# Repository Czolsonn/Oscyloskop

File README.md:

# Oscyloskop
Projekt amatorskiego oscyloskopu z wyświetlaczem LCD

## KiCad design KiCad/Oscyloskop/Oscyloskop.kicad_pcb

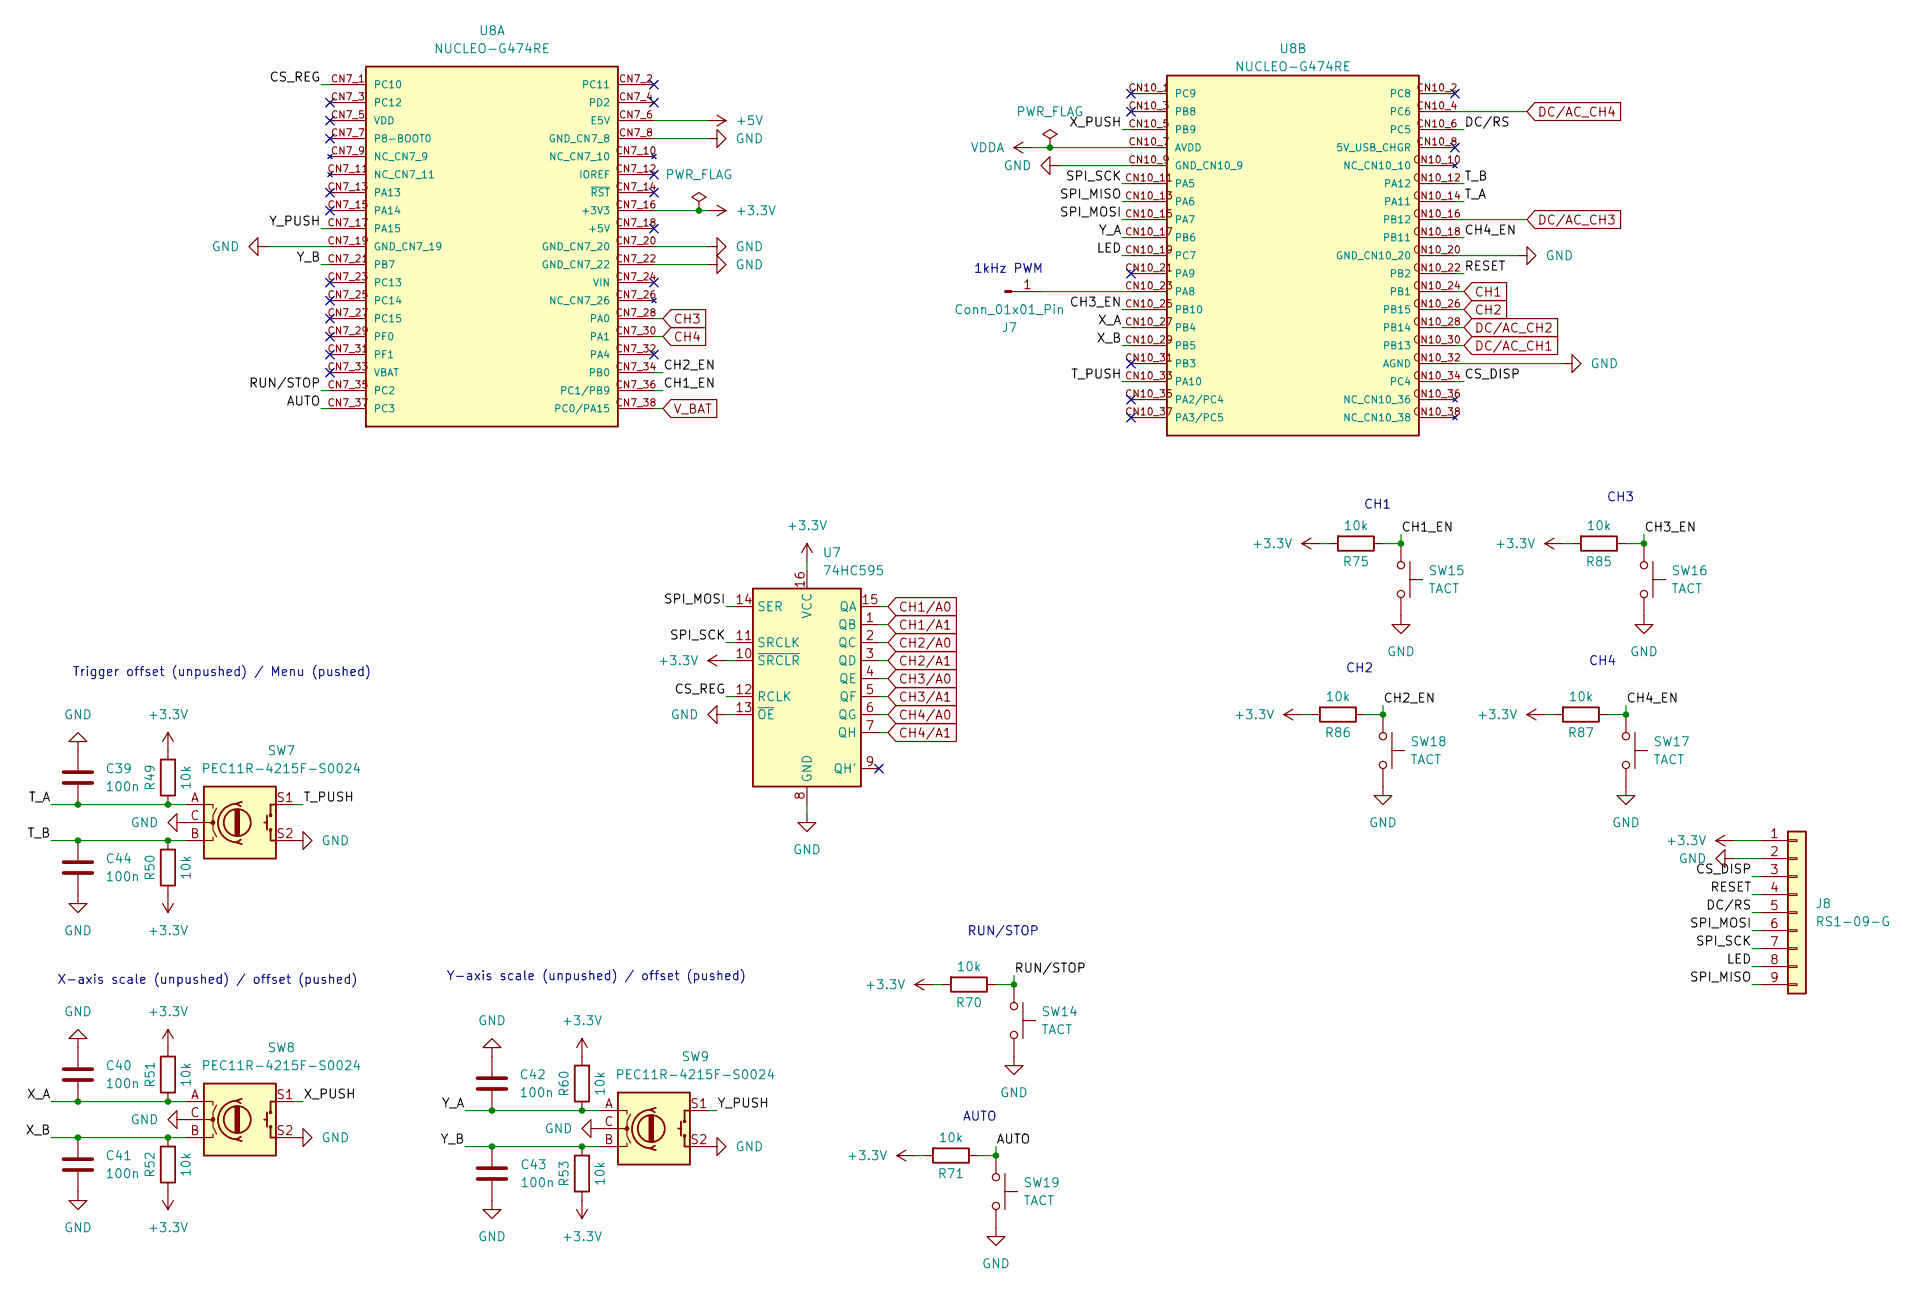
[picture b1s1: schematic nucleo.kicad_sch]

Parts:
C39, C40, C41, C42, C43, C44: 100n; C_0603_1608Metric
J7: Conn_01x01_Pin; PinHeader_1x01_P2.54mm_Vertical
J8: RS1-09-G; PinSocket_1x09_P2.54mm_Vertical
R49, R50, R51, R52, R53, R60, R70, R71, R75, R85, R86, R87: 10k; R_0603_1608Metric
SW7, SW8, SW9: PEC11R-4215F-S0024; RotaryEncoder_EC11_Switch_Vertical_Generic
SW14, SW15, SW16, SW17, SW18, SW19: TACT; SW_PUSH-12mm
U7: 74HC595; TSSOP-16_4.4x5mm_P0.65mm
U8: NUCLEO-G474RE; MODULE_NUCLEO-G474RE; PARTREV 17

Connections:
+3.3V: J8.1, R49.2, R50.1, R51.2, R52.1, R53.1, R60.2, R70.2, R71.2, R75.2, R85.2, R86.2, R87.2, U7.10 (~SRCLR), U7.16 (VCC), U8.CN7_16 (+3V3); also elsewhere on the board
+5V: U8.CN7_6 (E5V); also elsewhere on the board
/Nucleo STM32/AUTO: R71.1, SW19.1, U8.CN7_37 (PC3)
/Nucleo STM32/CH1_EN: R75.1, SW15.1, U8.CN7_36 (PC1/PB9)
/Nucleo STM32/CH2_EN: R86.1, SW18.1, U8.CN7_34 (PB0)
/Nucleo STM32/CH3_EN: R85.1, SW16.1, U8.CN10_25 (PB10)
/Nucleo STM32/CH4_EN: R87.1, SW17.1, U8.CN10_18 (PB11)
/Nucleo STM32/CS_DISP: J8.3, U8.CN10_34 (PC4)
/Nucleo STM32/CS_REG: U7.12 (RCLK), U8.CN7_1 (PC10)
/Nucleo STM32/DC/RS: J8.5, U8.CN10_6 (PC5)
/Nucleo STM32/LED: J8.8, U8.CN10_19 (PC7)
/Nucleo STM32/RESET: J8.4, U8.CN10_22 (PB2)
/Nucleo STM32/RUN/STOP: R70.1, SW14.1, U8.CN7_35 (PC2)
/Nucleo STM32/SPI_MISO: J8.9, U8.CN10_13 (PA6)
/Nucleo STM32/SPI_MOSI: J8.6, U7.14 (SER), U8.CN10_15 (PA7)
/Nucleo STM32/SPI_SCK: J8.7, U7.11 (SRCLK), U8.CN10_11 (PA5)
/Nucleo STM32/T_A: C39.1, R49.1, SW7.A, U8.CN10_14 (PA11)
/Nucleo STM32/T_B: C44.2, R50.2, SW7.B, U8.CN10_12 (PA12)
/Nucleo STM32/T_PUSH: SW7.S1, U8.CN10_33 (PA10)
/Nucleo STM32/X_A: C40.1, R51.1, SW8.A, U8.CN10_27 (PB4)
/Nucleo STM32/X_B: C41.2, R52.2, SW8.B, U8.CN10_29 (PB5)
/Nucleo STM32/X_PUSH: SW8.S1, U8.CN10_5 (PB9)
/Nucleo STM32/Y_A: C42.1, R60.1, SW9.A, U8.CN10_17 (PB6)
/Nucleo STM32/Y_B: C43.2, R53.2, SW9.B, U8.CN7_21 (PB7)
/Nucleo STM32/Y_PUSH: SW9.S1, U8.CN7_17 (PA15)
CH1: U8.CN10_24 (PB1); also elsewhere on the board
CH1/A0: U7.15 (QA); also elsewhere on the board
CH1/A1: U7.1 (QB); also elsewhere on the board
CH2: U8.CN10_26 (PB15); also elsewhere on the board
CH2/A0: U7.2 (QC); also elsewhere on the board
CH2/A1: U7.3 (QD); also elsewhere on the board
CH3: U8.CN7_28 (PA0); also elsewhere on the board
CH3/A0: U7.4 (QE); also elsewhere on the board
CH3/A1: U7.5 (QF); also elsewhere on the board
CH4: U8.CN7_30 (PA1); also elsewhere on the board
CH4/A0: U7.6 (QG); also elsewhere on the board
CH4/A1: U7.7 (QH); also elsewhere on the board
DC/AC_CH1: U8.CN10_30 (PB13); also elsewhere on the board
DC/AC_CH2: U8.CN10_28 (PB14); also elsewhere on the board
DC/AC_CH3: U8.CN10_16 (PB12); also elsewhere on the board
DC/AC_CH4: U8.CN10_4 (PC6); also elsewhere on the board
GND: C39.2, C40.2, C41.1, C42.2, C43.1, C44.1, J8.2, SW7.C, SW7.S2, SW8.C, SW8.S2, SW9.C, SW9.S2, SW14.2, SW15.2, SW16.2, SW17.2, SW18.2, SW19.2, U7.8 (GND), U7.13 (~OE), U8.CN7_8 (GND_CN7_8), U8.CN7_19 (GND_CN7_19), U8.CN7_20 (GND_CN7_20), U8.CN7_22 (GND_CN7_22), U8.CN10_9 (GND_CN10_9), U8.CN10_20 (GND_CN10_20), U8.CN10_32 (AGND); also elsewhere on the board
unnamed: J7.1 (Pin_1_1), U8.CN10_23 (PA8)
VDDA: U8.CN10_7 (AVDD); also elsewhere on the board
V_BAT: U8.CN7_38 (PC0/PA15); also elsewhere on the board

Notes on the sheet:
Y-axis scale (unpushed) / offset (pushed)
CH2
RUN/STOP
CH1
1kHz PWM
AUTO
CH4
X-axis scale (unpushed) / offset (pushed)
Trigger offset (unpushed) / Menu (pushed)
CH3

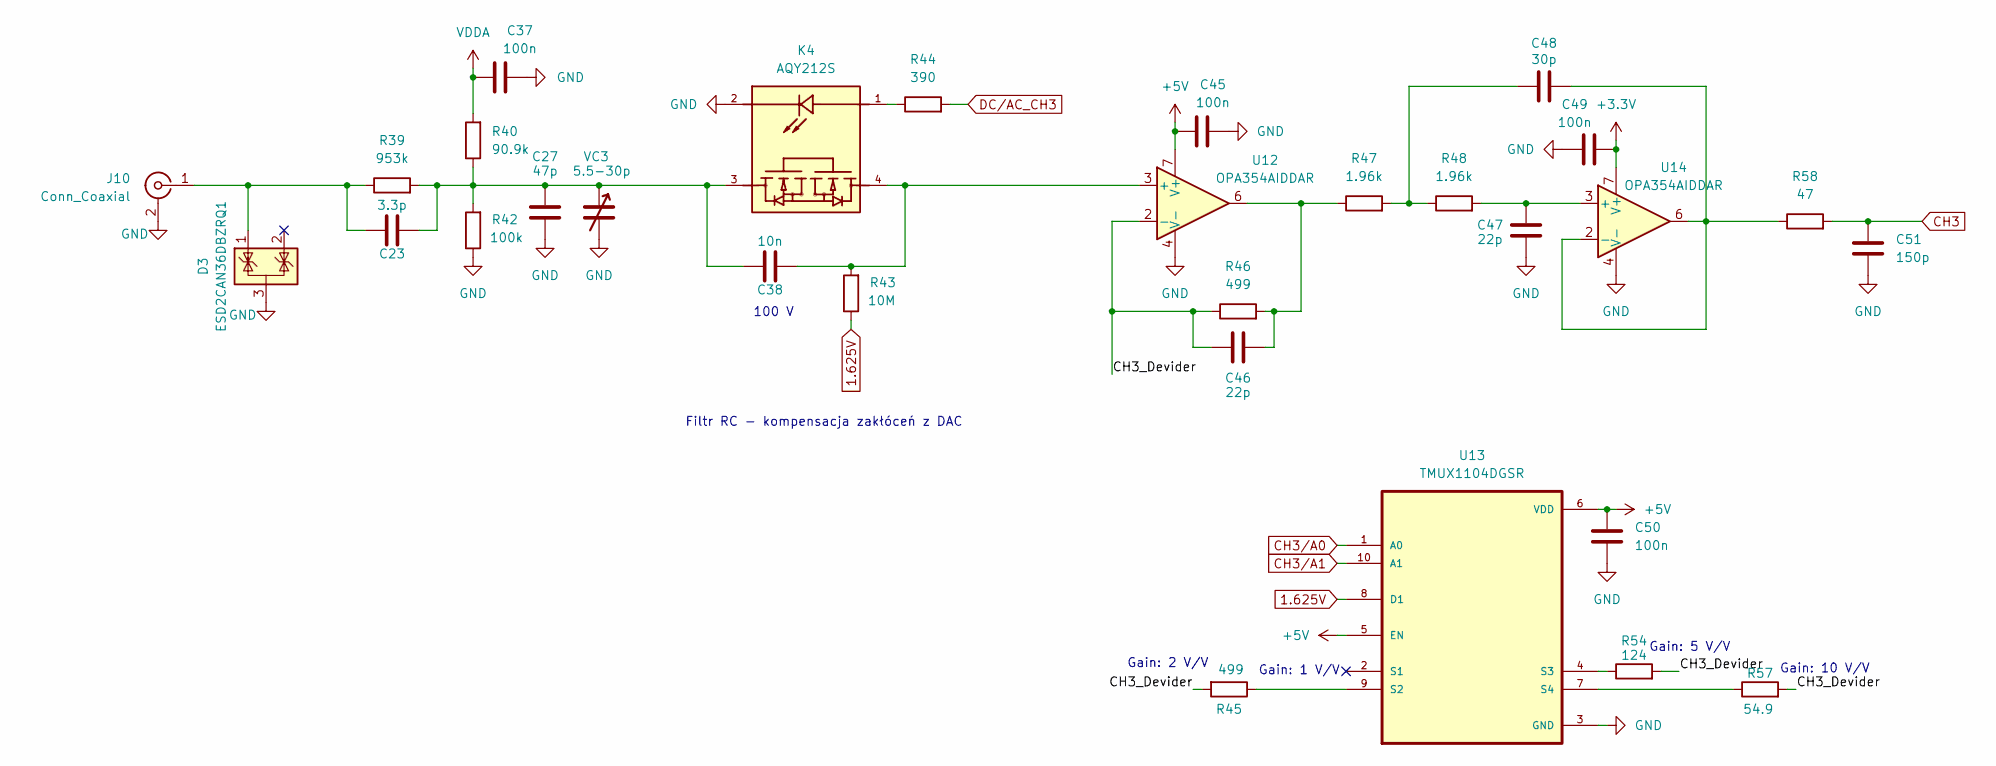
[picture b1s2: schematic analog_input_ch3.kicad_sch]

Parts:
C23: 3.3p; C_0603_1608Metric
C27: 47p; C_0603_1608Metric
C37, C45, C49, C50: 100n; C_0603_1608Metric
C38: 10n; C_0603_1608Metric
C46, C47: 22p; C_0603_1608Metric
C48: 30p; C_0603_1608Metric
C51: 150p; C_0603_1608Metric
D3: ESD2CAN36DBZRQ1; SOT-23
J10: Conn_Coaxial; BNC_Amphenol_B6252HB-NPP3G-50_Horizontal
K4: AQY212S; SOP-4_6.5x2.54; PART_NUMBER_(LCSC) C1525231
R39: 953k; R_0805_2012Metric
R40: 90.9k; R_0805_2012Metric
R42: 100k; R_0805_2012Metric
R43: 10M; R_0603_1608Metric
R44: 390; R_0603_1608Metric
R45, R46: 499; R_0603_1608Metric
R47, R48: 1.96k; R_0603_1608Metric
R54: 124; R_0603_1608Metric
R57: 54.9; R_0603_1608Metric
R58: 47; R_0603_1608Metric
U12, U14: OPA354AIDDAR; SOIC-8-1EP_3.9x4.9mm_P1.27mm_EP2.29x3mm
U13: TMUX1104DGSR; SOP50P490X110-10N
VC3: 5.5-30p; C_Trimmer_Voltronics_JZ

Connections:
1.625V: R43.1, U13.8 (D1); also elsewhere on the board
+3.3V: C49.2, U14.7 (V+); also elsewhere on the board
+5V: C45.1, C50.2, U12.7 (V+), U13.5 (EN), U13.6 (VDD); also elsewhere on the board
/Analog Input CH3/CH3_Devider: C46.2, R45.2, R46.1, R54.2, R57.2, U12.2 (-)
CH3: C51.1, R58.2; also elsewhere on the board
CH3/A0: U13.1 (A0); also elsewhere on the board
CH3/A1: U13.10 (A1); also elsewhere on the board
DC/AC_CH3: R44.2; also elsewhere on the board
GND: C27.1, C37.2, C45.2, C47.1, C49.1, C50.1, C51.2, D3.3 (A), J10.2 (Ext), K4.2, R42.1, U12.4 (V-), U12.9 (V-), U13.3 (GND), U14.4 (V-), U14.9 (V-), VC3.2; also elsewhere on the board
unnamed: C23.2, C27.2, C38.1, K4.3, R39.2, R40.1, R42.2, VC3.1
unnamed: C46.1, R46.2, R47.1, U12.6
unnamed: C48.1, R47.2, R48.1
unnamed: C23.1, D3.1 (K), J10.1 (In), R39.1
unnamed: K4.1, R44.1
unnamed: C38.2, K4.4, R43.2, U12.3 (+)
unnamed: R45.1, U13.9 (S2)
unnamed: R54.1, U13.4 (S3)
unnamed: R57.1, U13.7 (S4)
unnamed: C47.2, R48.2, U14.3 (+)
unnamed: C48.2, R58.1, U14.2 (-), U14.6
VDDA: C37.1, R40.2; also elsewhere on the board

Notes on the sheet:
Filtr RC - kompensacja zakłóceń z DAC
100 V
Gain: 2 V/V
Gain: 5 V/V
Gain: 1 V/V
Gain: 10 V/V

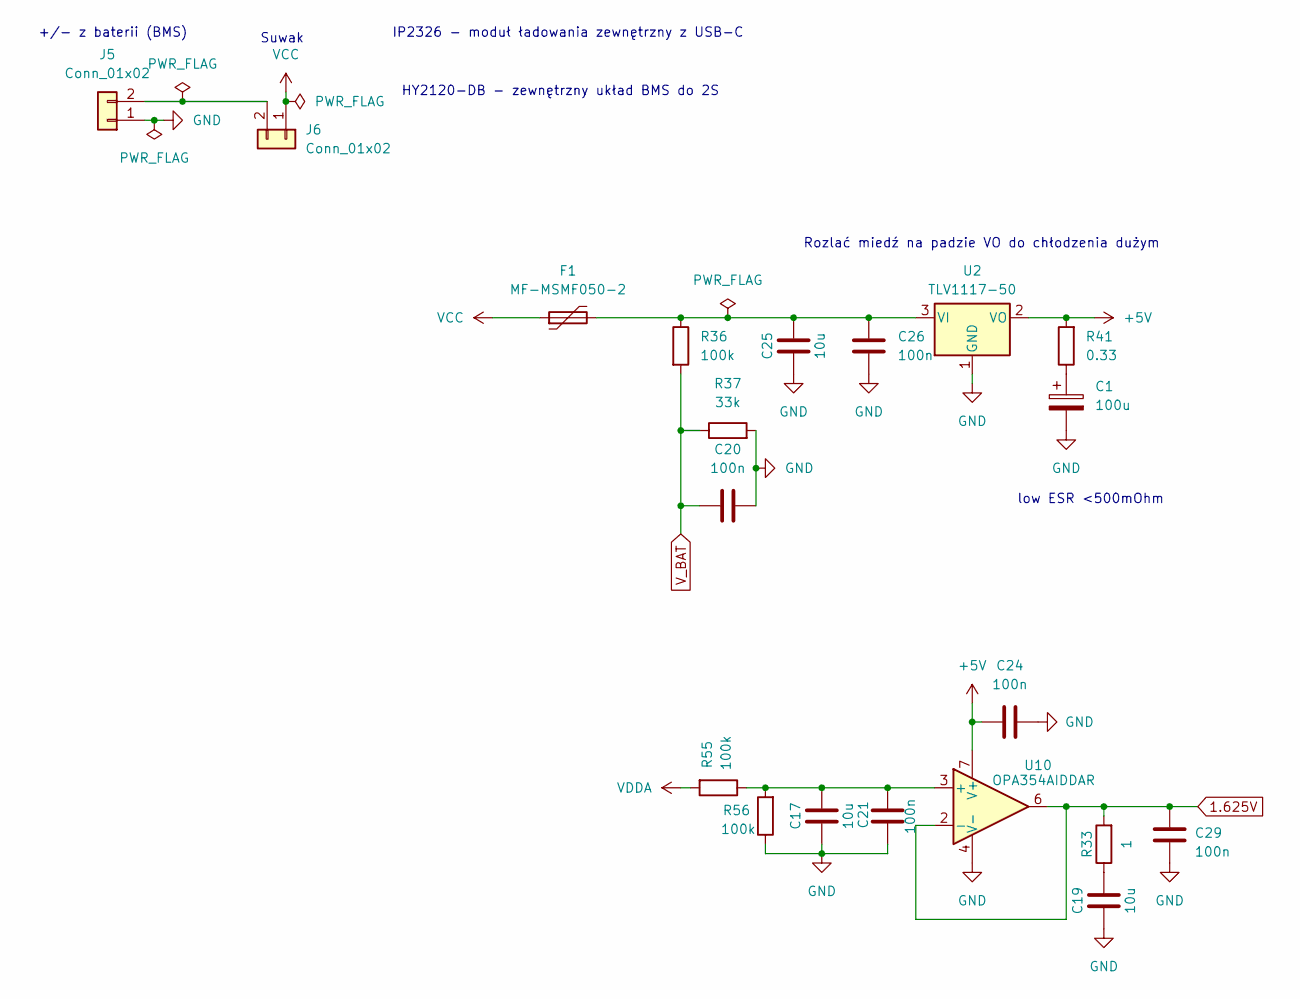
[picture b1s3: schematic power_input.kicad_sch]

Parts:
C1: 100u; CP_Elec_6.3x5.4
C17, C19, C25: 10u; C_0805_2012Metric
C20, C21, C24, C26, C29: 100n; C_0603_1608Metric
F1: MF-MSMF050-2; Fuse_1812_4532Metric
J5, J6: Conn_01x02; PinHeader_1x02_P2.54mm_Vertical
R33: 1; R_0603_1608Metric
R36: 100k; R_0603_1608Metric
R37: 33k; R_0603_1608Metric
R41: 0.33; R_0805_2012Metric
R55, R56: 100k; R_0805_2012Metric
U2: TLV1117-50; SOT-223-3_TabPin2
U10: OPA354AIDDAR; SOIC-8-1EP_3.9x4.9mm_P1.27mm_EP2.29x3mm

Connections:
1.625V: C29.2, R33.2, U10.2 (-), U10.6; also elsewhere on the board
+5V: C24.1, R41.2, U2.2 (VO), U10.7 (V+); also elsewhere on the board
GND: C1.2, C17.2, C19.2, C20.2, C21.2, C24.2, C25.2, C26.1, C29.1, J5.1, R37.2, R56.1, U2.1 (GND), U10.4 (V-), U10.9 (V-); also elsewhere on the board
unnamed: C1.1, R41.1
unnamed: C19.1, R33.1
unnamed: J5.2, J6.2
unnamed: C25.1, C26.2, F1.2, R36.1, U2.3 (VI)
unnamed: C17.1, C21.1, R55.1, R56.2, U10.3 (+)
VCC: F1.1, J6.1
VDDA: R55.2; also elsewhere on the board
V_BAT: C20.1, R36.2, R37.1; also elsewhere on the board

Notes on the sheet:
Rozlać miedź na padzie VO do chłodzenia dużym
HY2120-DB - zewnętrzny układ BMS do 2S
Suwak
IP2326 - moduł ładowania zewnętrzny z USB-C
low ESR <500mOhm
+/- z baterii (BMS)

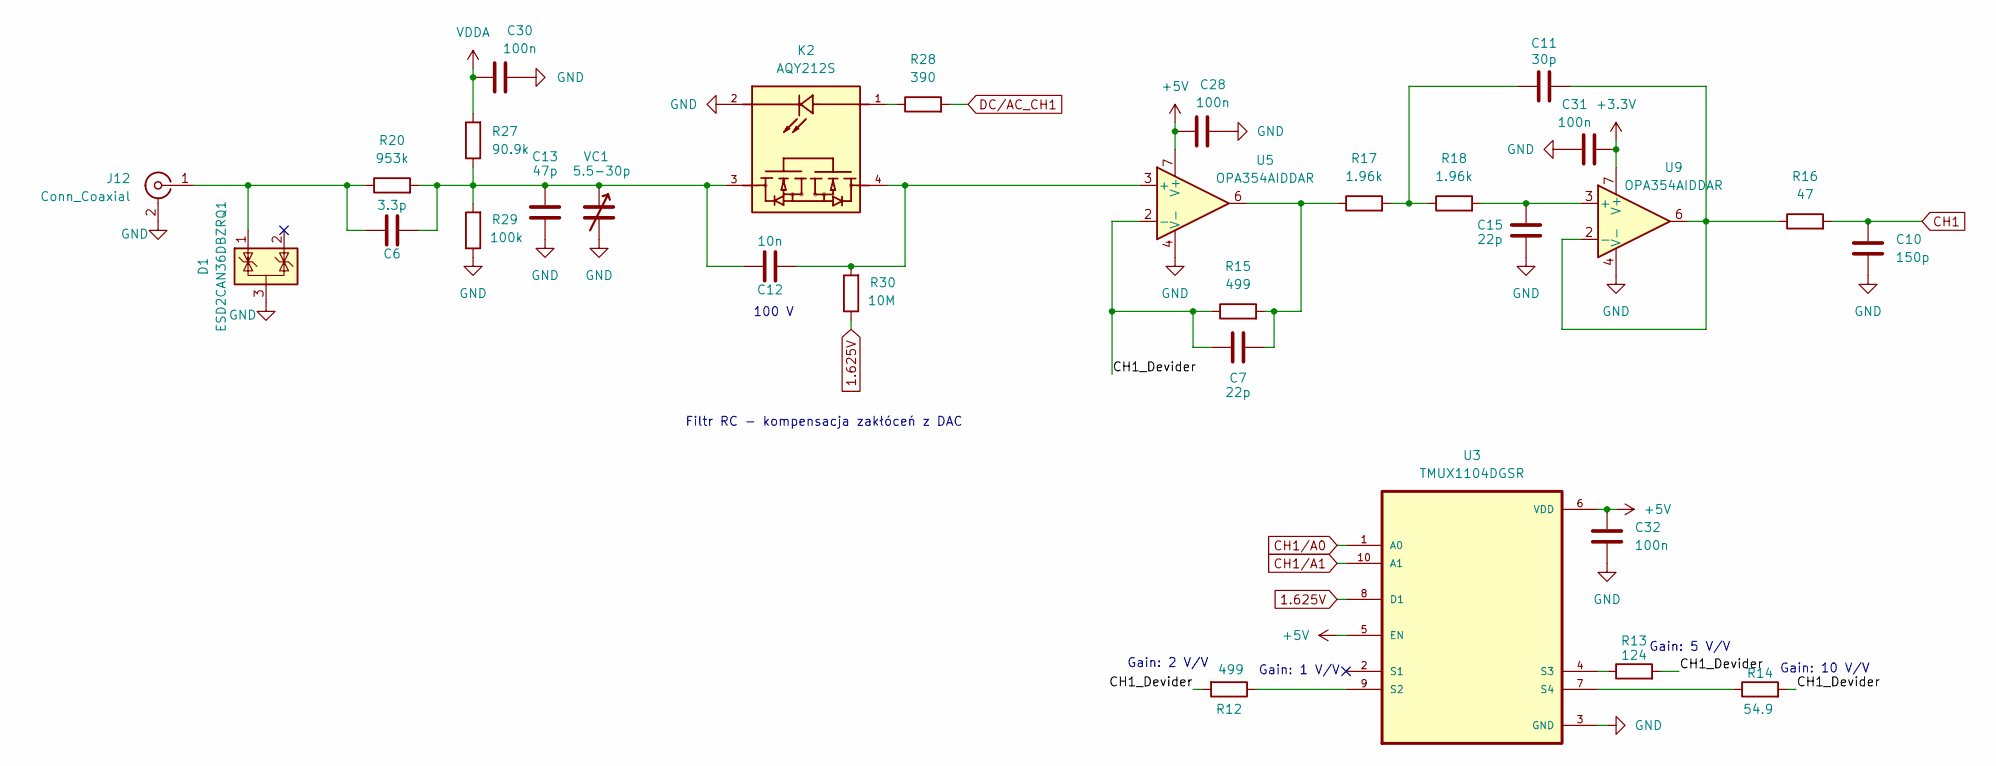
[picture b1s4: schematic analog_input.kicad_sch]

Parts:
C6: 3.3p; C_0603_1608Metric
C7, C15: 22p; C_0603_1608Metric
C10: 150p; C_0603_1608Metric
C11: 30p; C_0603_1608Metric
C12: 10n; C_0603_1608Metric
C13: 47p; C_0603_1608Metric
C28, C30, C31, C32: 100n; C_0603_1608Metric
D1: ESD2CAN36DBZRQ1; SOT-23
J12: Conn_Coaxial; BNC_Amphenol_B6252HB-NPP3G-50_Horizontal
K2: AQY212S; SOP-4_6.5x2.54; PART_NUMBER_(LCSC) C1525231
R12, R15: 499; R_0603_1608Metric
R13: 124; R_0603_1608Metric
R14: 54.9; R_0603_1608Metric
R16: 47; R_0603_1608Metric
R17, R18: 1.96k; R_0603_1608Metric
R20: 953k; R_0805_2012Metric
R27: 90.9k; R_0805_2012Metric
R28: 390; R_0603_1608Metric
R29: 100k; R_0805_2012Metric
R30: 10M; R_0603_1608Metric
U3: TMUX1104DGSR; SOP50P490X110-10N
U5, U9: OPA354AIDDAR; SOIC-8-1EP_3.9x4.9mm_P1.27mm_EP2.29x3mm
VC1: 5.5-30p; C_Trimmer_Voltronics_JZ

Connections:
1.625V: R30.1, U3.8 (D1); also elsewhere on the board
+3.3V: C31.2, U9.7 (V+); also elsewhere on the board
+5V: C28.1, C32.2, U3.5 (EN), U3.6 (VDD), U5.7 (V+); also elsewhere on the board
/Analog Input CH1/CH1_Devider: C7.2, R12.2, R13.2, R14.2, R15.1, U5.2 (-)
CH1: C10.1, R16.2; also elsewhere on the board
CH1/A0: U3.1 (A0); also elsewhere on the board
CH1/A1: U3.10 (A1); also elsewhere on the board
DC/AC_CH1: R28.2; also elsewhere on the board
GND: C10.2, C13.1, C15.1, C28.2, C30.2, C31.1, C32.1, D1.3 (A), J12.2 (Ext), K2.2, R29.1, U3.3 (GND), U5.4 (V-), U5.9 (V-), U9.4 (V-), U9.9 (V-), VC1.2; also elsewhere on the board
unnamed: C7.1, R15.2, R17.1, U5.6
unnamed: C11.1, R17.2, R18.1
unnamed: C6.2, C12.1, C13.2, K2.3, R20.2, R27.1, R29.2, VC1.1
unnamed: C6.1, D1.1 (K), J12.1 (In), R20.1
unnamed: K2.1, R28.1
unnamed: R12.1, U3.9 (S2)
unnamed: R13.1, U3.4 (S3)
unnamed: R14.1, U3.7 (S4)
unnamed: C12.2, K2.4, R30.2, U5.3 (+)
unnamed: C15.2, R18.2, U9.3 (+)
unnamed: C11.2, R16.1, U9.2 (-), U9.6
VDDA: C30.1, R27.2; also elsewhere on the board

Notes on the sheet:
Filtr RC - kompensacja zakłóceń z DAC
Gain: 10 V/V
Gain: 1 V/V
Gain: 2 V/V
100 V
Gain: 5 V/V

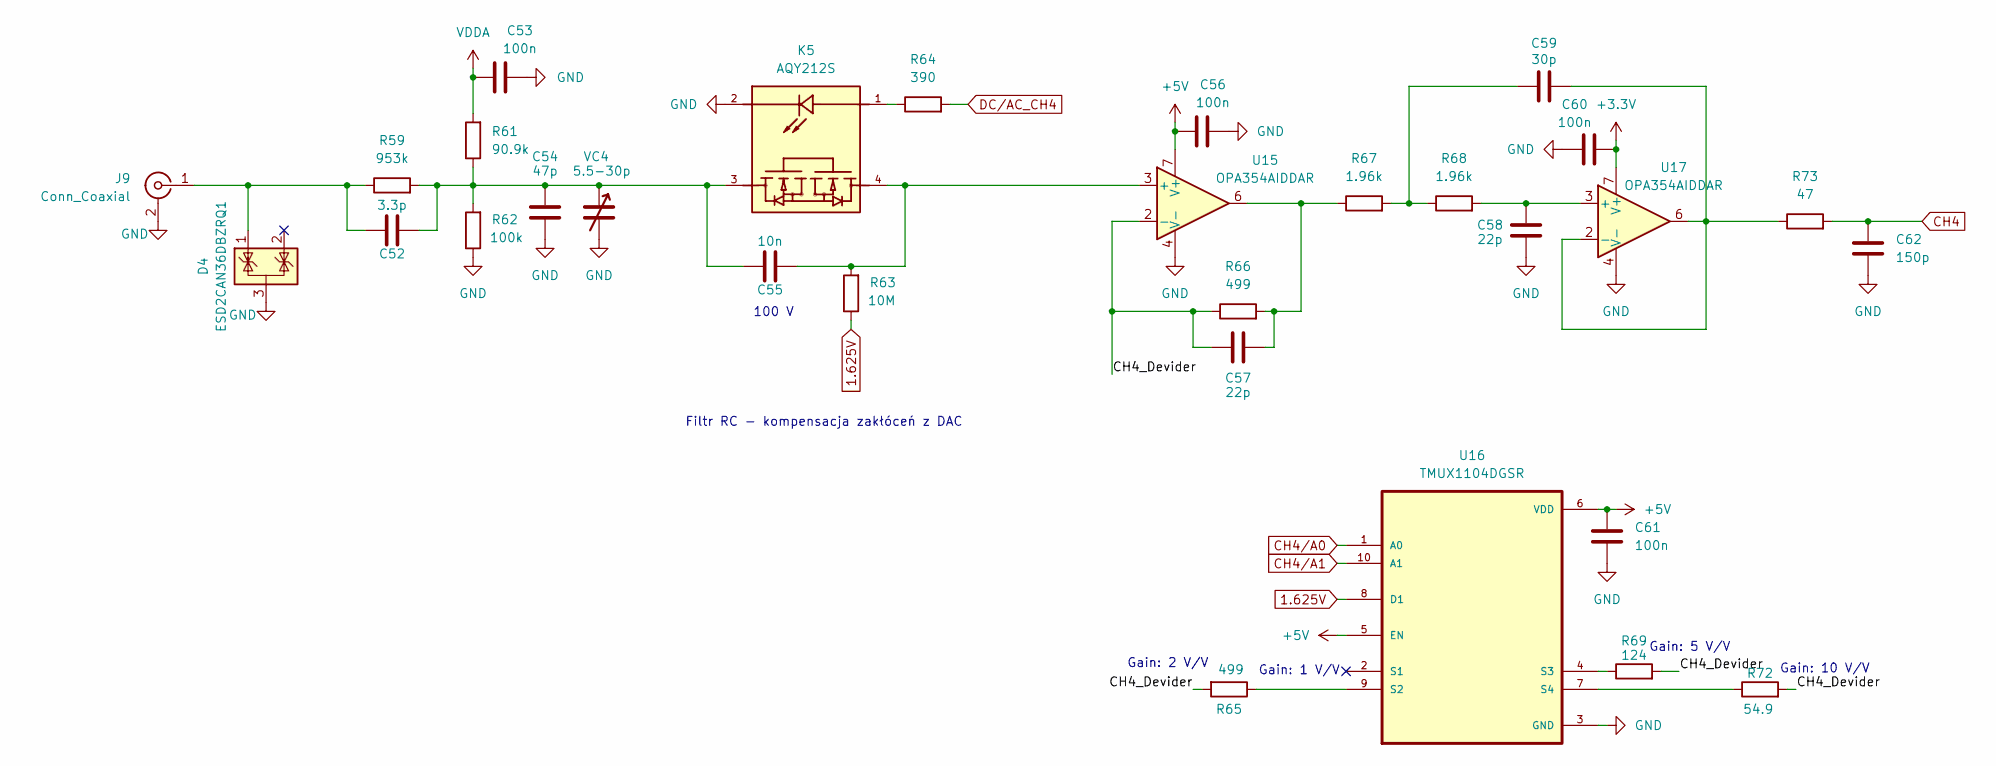
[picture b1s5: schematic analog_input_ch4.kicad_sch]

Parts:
C52: 3.3p; C_0603_1608Metric
C53, C56, C60, C61: 100n; C_0603_1608Metric
C54: 47p; C_0603_1608Metric
C55: 10n; C_0603_1608Metric
C57, C58: 22p; C_0603_1608Metric
C59: 30p; C_0603_1608Metric
C62: 150p; C_0603_1608Metric
D4: ESD2CAN36DBZRQ1; SOT-23
J9: Conn_Coaxial; BNC_Amphenol_B6252HB-NPP3G-50_Horizontal
K5: AQY212S; SOP-4_6.5x2.54; PART_NUMBER_(LCSC) C1525231
R59: 953k; R_0805_2012Metric
R61: 90.9k; R_0805_2012Metric
R62: 100k; R_0805_2012Metric
R63: 10M; R_0603_1608Metric
R64: 390; R_0603_1608Metric
R65, R66: 499; R_0603_1608Metric
R67, R68: 1.96k; R_0603_1608Metric
R69: 124; R_0603_1608Metric
R72: 54.9; R_0603_1608Metric
R73: 47; R_0603_1608Metric
U15, U17: OPA354AIDDAR; SOIC-8-1EP_3.9x4.9mm_P1.27mm_EP2.29x3mm
U16: TMUX1104DGSR; SOP50P490X110-10N
VC4: 5.5-30p; C_Trimmer_Voltronics_JZ

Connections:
1.625V: R63.1, U16.8 (D1); also elsewhere on the board
+3.3V: C60.2, U17.7 (V+); also elsewhere on the board
+5V: C56.1, C61.2, U15.7 (V+), U16.5 (EN), U16.6 (VDD); also elsewhere on the board
/Analog Input CH4/CH4_Devider: C57.2, R65.2, R66.1, R69.2, R72.2, U15.2 (-)
CH4: C62.1, R73.2; also elsewhere on the board
CH4/A0: U16.1 (A0); also elsewhere on the board
CH4/A1: U16.10 (A1); also elsewhere on the board
DC/AC_CH4: R64.2; also elsewhere on the board
GND: C53.2, C54.1, C56.2, C58.1, C60.1, C61.1, C62.2, D4.3 (A), J9.2 (Ext), K5.2, R62.1, U15.4 (V-), U15.9 (V-), U16.3 (GND), U17.4 (V-), U17.9 (V-), VC4.2; also elsewhere on the board
unnamed: C52.2, C54.2, C55.1, K5.3, R59.2, R61.1, R62.2, VC4.1
unnamed: C57.1, R66.2, R67.1, U15.6
unnamed: C59.1, R67.2, R68.1
unnamed: C52.1, D4.1 (K), J9.1 (In), R59.1
unnamed: K5.1, R64.1
unnamed: C55.2, K5.4, R63.2, U15.3 (+)
unnamed: R65.1, U16.9 (S2)
unnamed: R69.1, U16.4 (S3)
unnamed: R72.1, U16.7 (S4)
unnamed: C58.2, R68.2, U17.3 (+)
unnamed: C59.2, R73.1, U17.2 (-), U17.6
VDDA: C53.1, R61.2; also elsewhere on the board

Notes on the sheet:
Gain: 2 V/V
Filtr RC - kompensacja zakłóceń z DAC
Gain: 5 V/V
Gain: 1 V/V
Gain: 10 V/V
100 V

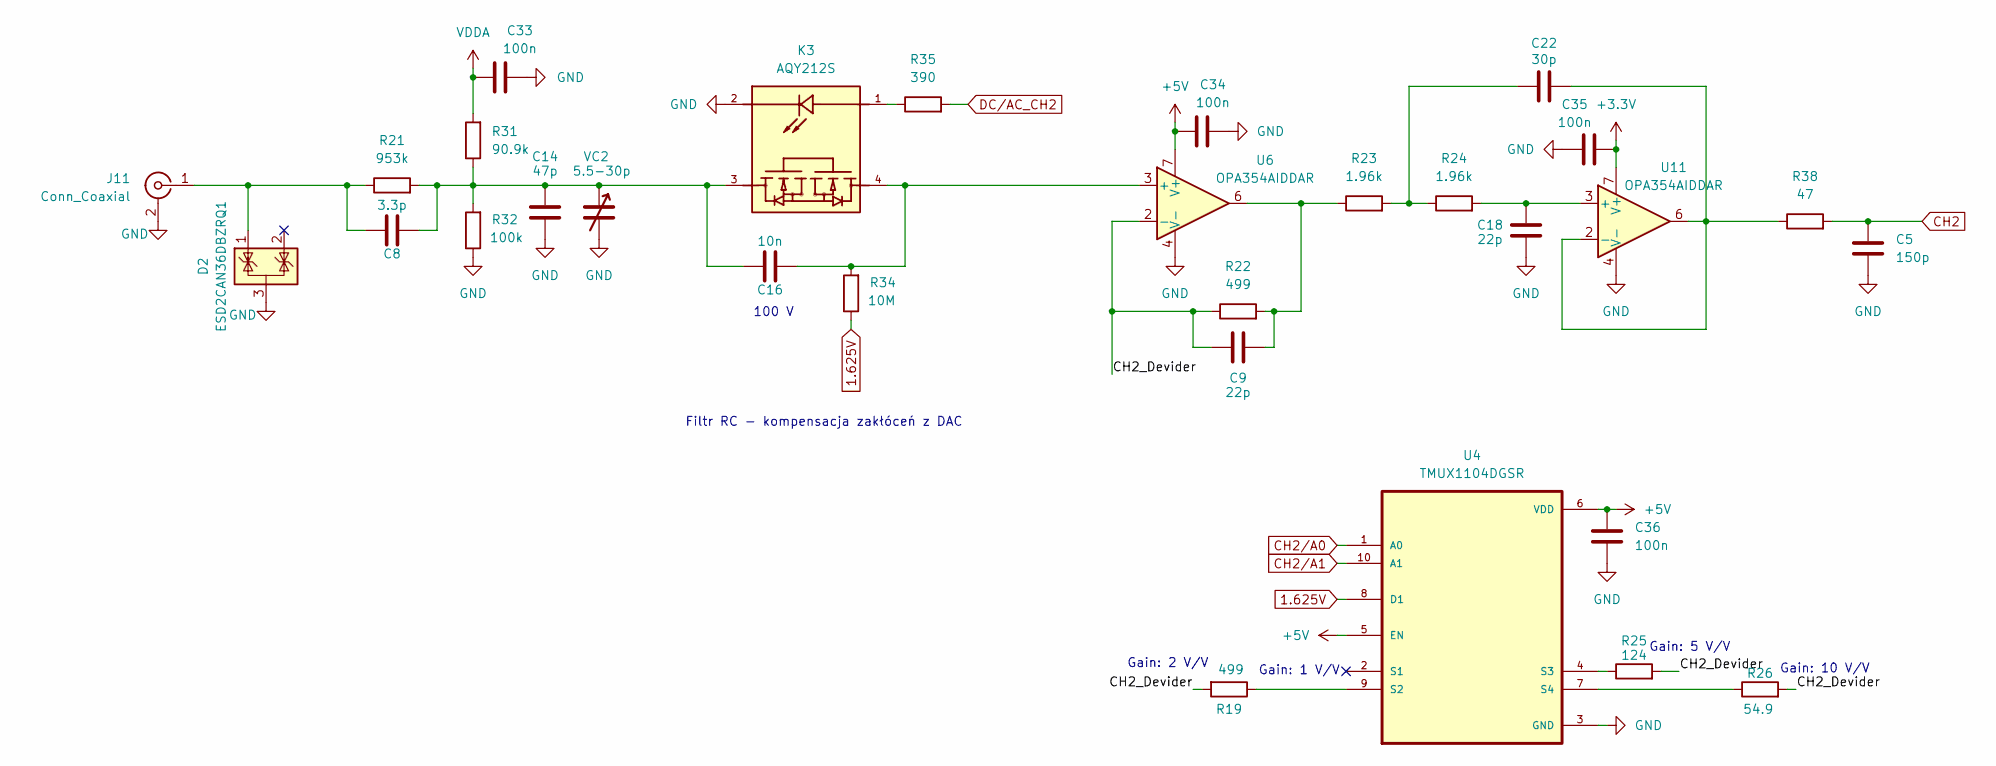
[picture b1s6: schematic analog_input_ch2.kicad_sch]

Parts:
C5: 150p; C_0603_1608Metric
C8: 3.3p; C_0603_1608Metric
C9, C18: 22p; C_0603_1608Metric
C14: 47p; C_0603_1608Metric
C16: 10n; C_0603_1608Metric
C22: 30p; C_0603_1608Metric
C33, C34, C35, C36: 100n; C_0603_1608Metric
D2: ESD2CAN36DBZRQ1; SOT-23
J11: Conn_Coaxial; BNC_Amphenol_B6252HB-NPP3G-50_Horizontal
K3: AQY212S; SOP-4_6.5x2.54; PART_NUMBER_(LCSC) C1525231
R19, R22: 499; R_0603_1608Metric
R21: 953k; R_0805_2012Metric
R23, R24: 1.96k; R_0603_1608Metric
R25: 124; R_0603_1608Metric
R26: 54.9; R_0603_1608Metric
R31: 90.9k; R_0805_2012Metric
R32: 100k; R_0805_2012Metric
R34: 10M; R_0603_1608Metric
R35: 390; R_0603_1608Metric
R38: 47; R_0603_1608Metric
U4: TMUX1104DGSR; SOP50P490X110-10N
U6, U11: OPA354AIDDAR; SOIC-8-1EP_3.9x4.9mm_P1.27mm_EP2.29x3mm
VC2: 5.5-30p; C_Trimmer_Voltronics_JZ

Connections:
1.625V: R34.1, U4.8 (D1); also elsewhere on the board
+3.3V: C35.2, U11.7 (V+); also elsewhere on the board
+5V: C34.1, C36.2, U4.5 (EN), U4.6 (VDD), U6.7 (V+); also elsewhere on the board
/Analog Input CH2/CH2_Devider: C9.2, R19.2, R22.1, R25.2, R26.2, U6.2 (-)
CH2: C5.1, R38.2; also elsewhere on the board
CH2/A0: U4.1 (A0); also elsewhere on the board
CH2/A1: U4.10 (A1); also elsewhere on the board
DC/AC_CH2: R35.2; also elsewhere on the board
GND: C5.2, C14.1, C18.1, C33.2, C34.2, C35.1, C36.1, D2.3 (A), J11.2 (Ext), K3.2, R32.1, U4.3 (GND), U6.4 (V-), U6.9 (V-), U11.4 (V-), U11.9 (V-), VC2.2; also elsewhere on the board
unnamed: C9.1, R22.2, R23.1, U6.6
unnamed: C8.2, C14.2, C16.1, K3.3, R21.2, R31.1, R32.2, VC2.1
unnamed: C22.1, R23.2, R24.1
unnamed: C8.1, D2.1 (K), J11.1 (In), R21.1
unnamed: K3.1, R35.1
unnamed: R19.1, U4.9 (S2)
unnamed: R25.1, U4.4 (S3)
unnamed: R26.1, U4.7 (S4)
unnamed: C16.2, K3.4, R34.2, U6.3 (+)
unnamed: C18.2, R24.2, U11.3 (+)
unnamed: C22.2, R38.1, U11.2 (-), U11.6
VDDA: C33.1, R31.2; also elsewhere on the board

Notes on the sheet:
Filtr RC - kompensacja zakłóceń z DAC
100 V
Gain: 1 V/V
Gain: 2 V/V
Gain: 5 V/V
Gain: 10 V/V

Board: 2 copper layers, 171 parts (0 on the bottom side), 100 nets, no tracks yet.

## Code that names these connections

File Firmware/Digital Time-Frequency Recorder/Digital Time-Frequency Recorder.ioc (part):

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Mcu.Name=STM32G474R(B-C-E)Tx
Mcu.Package=LQFP64
Mcu.UserName=STM32G474RETx
PA0.GPIOParameters=GPIO_Label
PA0.GPIO_Label=CH3
PA0.Mode=IN1-Single-Ended
PA0.Signal=ADC1_IN1
PA1.GPIOParameters=GPIO_Label
PA1.GPIO_Label=CH4
PA1.Mode=IN2-Single-Ended
PA1.Signal=ADC2_IN2
PA10.GPIOParameters=GPIO_Label
PA10.GPIO_Label=T_PUSH
PA10.Signal=GPIO_Input
PA11.GPIOParameters=GPIO_Label
PA11.GPIO_Label=T_A
PA11.Signal=S_TIM4_CH1
PA12.GPIOParameters=GPIO_Label
PA12.GPIO_Label=T_B
PA12.Signal=S_TIM4_CH2
PA13.GPIOParameters=GPIO_Label
PA13.GPIO_Label=T_SWDIO
PA13.Mode=Serial_Wire
PA13.Signal=SYS_JTMS-SWDIO
PA14.GPIOParameters=GPIO_Label
PA14.GPIO_Label=T_SWCLK
PA14.Mode=Serial_Wire
PA14.Signal=SYS_JTCK-SWCLK
PA15.GPIOParameters=GPIO_Label
PA15.GPIO_Label=Y_PUSH
PA15.Signal=GPIO_Input
PA2.Mode=Asynchronous
PA2.Signal=LPUART1_TX
PA3.Mode=Asynchronous
PA3.Signal=LPUART1_RX
PA4.Signal=COMP_DAC11_group
PA5.GPIOParameters=GPIO_Speed
PA5.GPIO_Speed=GPIO_SPEED_FREQ_VERY_HIGH
PA5.Mode=Full_Duplex_Master
PA5.Signal=SPI1_SCK
PA6.GPIOParameters=GPIO_Speed
PA6.GPIO_Speed=GPIO_SPEED_FREQ_VERY_HIGH
PA6.Mode=Full_Duplex_Master
PA6.Signal=SPI1_MISO
PA7.GPIOParameters=GPIO_Speed
PA7.GPIO_Speed=GPIO_SPEED_FREQ_VERY_HIGH
PA7.Mode=Full_Duplex_Master
PA7.Signal=SPI1_MOSI
PB0.GPIOParameters=GPIO_Label
PB0.GPIO_Label=CH4_EN
PB0.Signal=GPIO_Input
PB1.GPIOParameters=GPIO_Label
PB1.GPIO_Label=CH1
PB1.Mode=IN1-Single-Ended
PB1.Signal=ADC3_IN1
PB10.GPIOParameters=GPIO_Label
PB10.GPIO_Label=CH2_EN
PB10.Signal=GPIO_Input
PB11.GPIOParameters=GPIO_Label
PB11.GPIO_Label=CH3_EN
PB11.Signal=GPIO_Input
PB12.GPIOParameters=GPIO_Label
PB12.GPIO_Label=DCAC_CH3
PB12.Signal=GPIO_Output
PB13.GPIOParameters=GPIO_Label
PB13.GPIO_Label=DCAC_CH1
PB13.Signal=GPIO_Output
PB14.GPIOParameters=GPIO_Label
PB14.GPIO_Label=DCAC_CH2
PB14.Signal=GPIO_Output
PB15.GPIOParameters=GPIO_Label
PB15.GPIO_Label=CH2
PB15.Mode=IN5-Single-Ended
PB15.Signal=ADC4_IN5
PB3.GPIOParameters=GPIO_Label
PB3.GPIO_Label=T_SWO
PB3.Signal=SYS_JTDO-SWO
PB4.GPIOParameters=GPIO_Label
PB4.GPIO_Label=X_A
PB4.Signal=S_TIM3_CH1
PB5.GPIOParameters=GPIO_Label
PB5.GPIO_Label=X_B
PB5.Signal=S_TIM3_CH2
PB6.GPIOParameters=GPIO_Label
PB6.GPIO_Label=Y_A
PB6.Signal=GPIO_Input
PB7.GPIOParameters=GPIO_Label
PB7.GPIO_Label=Y_B
PB7.Signal=GPIO_Input
PB9.GPIOParameters=GPIO_Label
PB9.GPIO_Label=X_PUSH
PB9.Signal=GPIO_Input
PC0.GPIOParameters=GPIO_Label
PC0.GPIO_Label=V_BAT
PC0.Mode=IN6-Single-Ended
PC0.Signal=ADC1_IN6
PC1.GPIOParameters=GPIO_Label
PC1.GPIO_Label=CH1_EN
PC1.Signal=GPIO_Input
PC10.GPIOParameters=PinState,GPIO_Label
PC10.GPIO_Label=CS_REG
PC10.PinState=GPIO_PIN_SET
PC10.Signal=GPIO_Output
PC11.GPIOParameters=GPIO_Label
PC11.GPIO_Label=DC/RS
PC11.Signal=GPIO_Output
PC12.GPIOParameters=GPIO_Label
PC12.GPIO_Label=CAL_1KHZ
PC12.Signal=S_TIM5_CH2
PC14-OSC32_IN.GPIOParameters=GPIO_Label
PC14-OSC32_IN.GPIO_Label=RCC_OSC32_IN
PC14-OSC32_IN.Signal=RCC_OSC32_IN
PC15-OSC32_OUT.GPIOParameters=GPIO_Label
PC15-OSC32_OUT.GPIO_Label=RCC_OSC32_OUT
PC15-OSC32_OUT.Signal=RCC_OSC32_OUT
PC2.GPIOParameters=GPIO_Label
PC2.GPIO_Label=RUN_STOP
PC2.Signal=GPIO_Input
PC3.GPIOParameters=GPIO_Label
PC3.GPIO_Label=AUTO
PC3.Signal=GPIO_Input
PC4.GPIOParameters=PinState,GPIO_Label
PC4.GPIO_Label=CS_DISP
PC4.PinState=GPIO_PIN_SET
PC4.Signal=GPIO_Output
PC6.GPIOParameters=GPIO_Label
PC6.GPIO_Label=DCAC_CH4
PC6.Signal=GPIO_Output
PC7.GPIOParameters=GPIO_Label
PC7.GPIO_Label=LED
PC7.Signal=S_TIM8_CH2
PD2.GPIOParameters=PinState,GPIO_Label
PD2.GPIO_Label=RESET
PD2.PinState=GPIO_PIN_SET
PD2.Signal=GPIO_Output
PF0-OSC_IN.GPIOParameters=GPIO_Label
PF0-OSC_IN.GPIO_Label=RCC_OSC_IN
PF0-OSC_IN.Mode=HSE-External-Oscillator
PF0-OSC_IN.Signal=RCC_OSC_IN
PF1-OSC_OUT.GPIOParameters=GPIO_Label
PF1-OSC_OUT.GPIO_Label=RCC_OSC_OUT
PF1-OSC_OUT.Mode=HSE-External-Oscillator
PF1-OSC_OUT.Signal=RCC_OSC_OUT
RCC.HSE_VALUE=24000000
RCC.SYSCLKFreq_VALUE=156000000
RCC.SYSCLKSource=RCC_SYSCLKSOURCE_PLLCLK
board=NUCLEO-G474RE
boardIOC=true

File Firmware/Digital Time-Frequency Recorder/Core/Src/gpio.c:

/* USER CODE BEGIN Header */
/**
  ******************************************************************************
  * @file    gpio.c
  * @brief   This file provides code for the configuration
  *          of all used GPIO pins.
  ******************************************************************************
  * @attention
  *
  * Copyright (c) 2026 STMicroelectronics.
  * All rights reserved.
  *
  * This software is licensed under terms that can be found in the LICENSE file
  * in the root directory of this software component.
  * If no LICENSE file comes with this software, it is provided AS-IS.
  *
  ******************************************************************************
  */
/* USER CODE END Header */

/* Includes ------------------------------------------------------------------*/
#include "gpio.h"

/* USER CODE BEGIN 0 */

/* USER CODE END 0 */

/*----------------------------------------------------------------------------*/
/* Configure GPIO                                                             */
/*----------------------------------------------------------------------------*/
/* USER CODE BEGIN 1 */

/* USER CODE END 1 */

/** Configure pins as
        * Analog
        * Input
        * Output
        * EVENT_OUT
        * EXTI
        * Free pins are configured automatically as Analog (this feature is enabled through
        * the Code Generation settings)
*/
void MX_GPIO_Init(void)
{

  GPIO_InitTypeDef GPIO_InitStruct = {0};

  /* GPIO Ports Clock Enable */
  __HAL_RCC_GPIOC_CLK_ENABLE();
  __HAL_RCC_GPIOF_CLK_ENABLE();
  __HAL_RCC_GPIOG_CLK_ENABLE();
  __HAL_RCC_GPIOA_CLK_ENABLE();
  __HAL_RCC_GPIOB_CLK_ENABLE();
  __HAL_RCC_GPIOD_CLK_ENABLE();

  /*Configure GPIO pin Output Level */
  HAL_GPIO_WritePin(GPIOC, CS_DISP_Pin|CS_REG_Pin, GPIO_PIN_SET);

  /*Configure GPIO pin Output Level */
  HAL_GPIO_WritePin(GPIOB, DCAC_CH3_Pin|DCAC_CH1_Pin|DCAC_CH2_Pin, GPIO_PIN_RESET);

  /*Configure GPIO pin Output Level */
  HAL_GPIO_WritePin(GPIOC, DCAC_CH4_Pin|DC_RS_Pin, GPIO_PIN_RESET);

  /*Configure GPIO pin Output Level */
  HAL_GPIO_WritePin(RESET_GPIO_Port, RESET_Pin, GPIO_PIN_SET);

  /*Configure GPIO pins : PC13 PC5 PC8 PC9 */
  GPIO_InitStruct.Pin = GPIO_PIN_13|GPIO_PIN_5|GPIO_PIN_8|GPIO_PIN_9;
  GPIO_InitStruct.Mode = GPIO_MODE_ANALOG;
  GPIO_InitStruct.Pull = GPIO_NOPULL;
  HAL_GPIO_Init(GPIOC, &GPIO_InitStruct);

  /*Configure GPIO pin : PG10 */
  GPIO_InitStruct.Pin = GPIO_PIN_10;
  GPIO_InitStruct.Mode = GPIO_MODE_ANALOG;
  GPIO_InitStruct.Pull = GPIO_NOPULL;
  HAL_GPIO_Init(GPIOG, &GPIO_InitStruct);

  /*Configure GPIO pins : CH1_EN_Pin RUN_STOP_Pin AUTO_Pin */
  GPIO_InitStruct.Pin = CH1_EN_Pin|RUN_STOP_Pin|AUTO_Pin;
  GPIO_InitStruct.Mode = GPIO_MODE_INPUT;
  GPIO_InitStruct.Pull = GPIO_NOPULL;
  HAL_GPIO_Init(GPIOC, &GPIO_InitStruct);

  /*Configure GPIO pins : CS_DISP_Pin DCAC_CH4_Pin CS_REG_Pin DC_RS_Pin */
  GPIO_InitStruct.Pin = CS_DISP_Pin|DCAC_CH4_Pin|CS_REG_Pin|DC_RS_Pin;
  GPIO_InitStruct.Mode = GPIO_MODE_OUTPUT_PP;
  GPIO_InitStruct.Pull = GPIO_NOPULL;
  GPIO_InitStruct.Speed = GPIO_SPEED_FREQ_LOW;
  HAL_GPIO_Init(GPIOC, &GPIO_InitStruct);

  /*Configure GPIO pins : CH4_EN_Pin CH2_EN_Pin CH3_EN_Pin Y_A_Pin
                           Y_B_Pin X_PUSH_Pin */
  GPIO_InitStruct.Pin = CH4_EN_Pin|CH2_EN_Pin|CH3_EN_Pin|Y_A_Pin
                          |Y_B_Pin|X_PUSH_Pin;
  GPIO_InitStruct.Mode = GPIO_MODE_INPUT;
  GPIO_InitStruct.Pull = GPIO_NOPULL;
  HAL_GPIO_Init(GPIOB, &GPIO_InitStruct);

  /*Configure GPIO pins : PB2 PB8 */
  GPIO_InitStruct.Pin = GPIO_PIN_2|GPIO_PIN_8;
  GPIO_InitStruct.Mode = GPIO_MODE_ANALOG;
  GPIO_InitStruct.Pull = GPIO_NOPULL;
  HAL_GPIO_Init(GPIOB, &GPIO_InitStruct);

  /*Configure GPIO pins : DCAC_CH3_Pin DCAC_CH1_Pin DCAC_CH2_Pin */
  GPIO_InitStruct.Pin = DCAC_CH3_Pin|DCAC_CH1_Pin|DCAC_CH2_Pin;
  GPIO_InitStruct.Mode = GPIO_MODE_OUTPUT_PP;
  GPIO_InitStruct.Pull = GPIO_NOPULL;
  GPIO_InitStruct.Speed = GPIO_SPEED_FREQ_LOW;
  HAL_GPIO_Init(GPIOB, &GPIO_InitStruct);

  /*Configure GPIO pins : PA8 PA9 */
  GPIO_InitStruct.Pin = GPIO_PIN_8|GPIO_PIN_9;
  GPIO_InitStruct.Mode = GPIO_MODE_ANALOG;
  GPIO_InitStruct.Pull = GPIO_NOPULL;
  HAL_GPIO_Init(GPIOA, &GPIO_InitStruct);

  /*Configure GPIO pins : T_PUSH_Pin Y_PUSH_Pin */
  GPIO_InitStruct.Pin = T_PUSH_Pin|Y_PUSH_Pin;
  GPIO_InitStruct.Mode = GPIO_MODE_INPUT;
  GPIO_InitStruct.Pull = GPIO_NOPULL;
  HAL_GPIO_Init(GPIOA, &GPIO_InitStruct);

  /*Configure GPIO pin : RESET_Pin */
  GPIO_InitStruct.Pin = RESET_Pin;
  GPIO_InitStruct.Mode = GPIO_MODE_OUTPUT_PP;
  GPIO_InitStruct.Pull = GPIO_NOPULL;
  GPIO_InitStruct.Speed = GPIO_SPEED_FREQ_LOW;
  HAL_GPIO_Init(RESET_GPIO_Port, &GPIO_InitStruct);

}

/* USER CODE BEGIN 2 */

/* USER CODE END 2 */

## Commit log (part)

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2026-02-20 Symulacja 20.02
    Dodano: symulacje wyidealizowanego układu do przetwarzania sygnału mierzonego przez oscyloskop
    Zmiany:
    .gitignore dodano LTSpice ignore
2026-02-21 LMH6643
    Dobór wzmacniacza operacyjnego do układu: LMH6643 i symulacja w LT Spice dla nowego wzmacniacza i zmiana rezystorów odpowiednich do układów
2026-03-15 KiCAD - schemat i STM32CubeMX - konfiguracja pinów
    Opis zmian:
    1) KiCAD
    - Podział na Analog Input, STM32 i Power Input
    - Pierwotny schemat z elementami Analog input dla channel 1
    - Dobór STM32G474CET jako mikrokontroler do przetwarzania i wyświetlania sygnałów
    - Wyprowadzenia pinów mikrokontrolera w tym dla programatora ST-LINK3
